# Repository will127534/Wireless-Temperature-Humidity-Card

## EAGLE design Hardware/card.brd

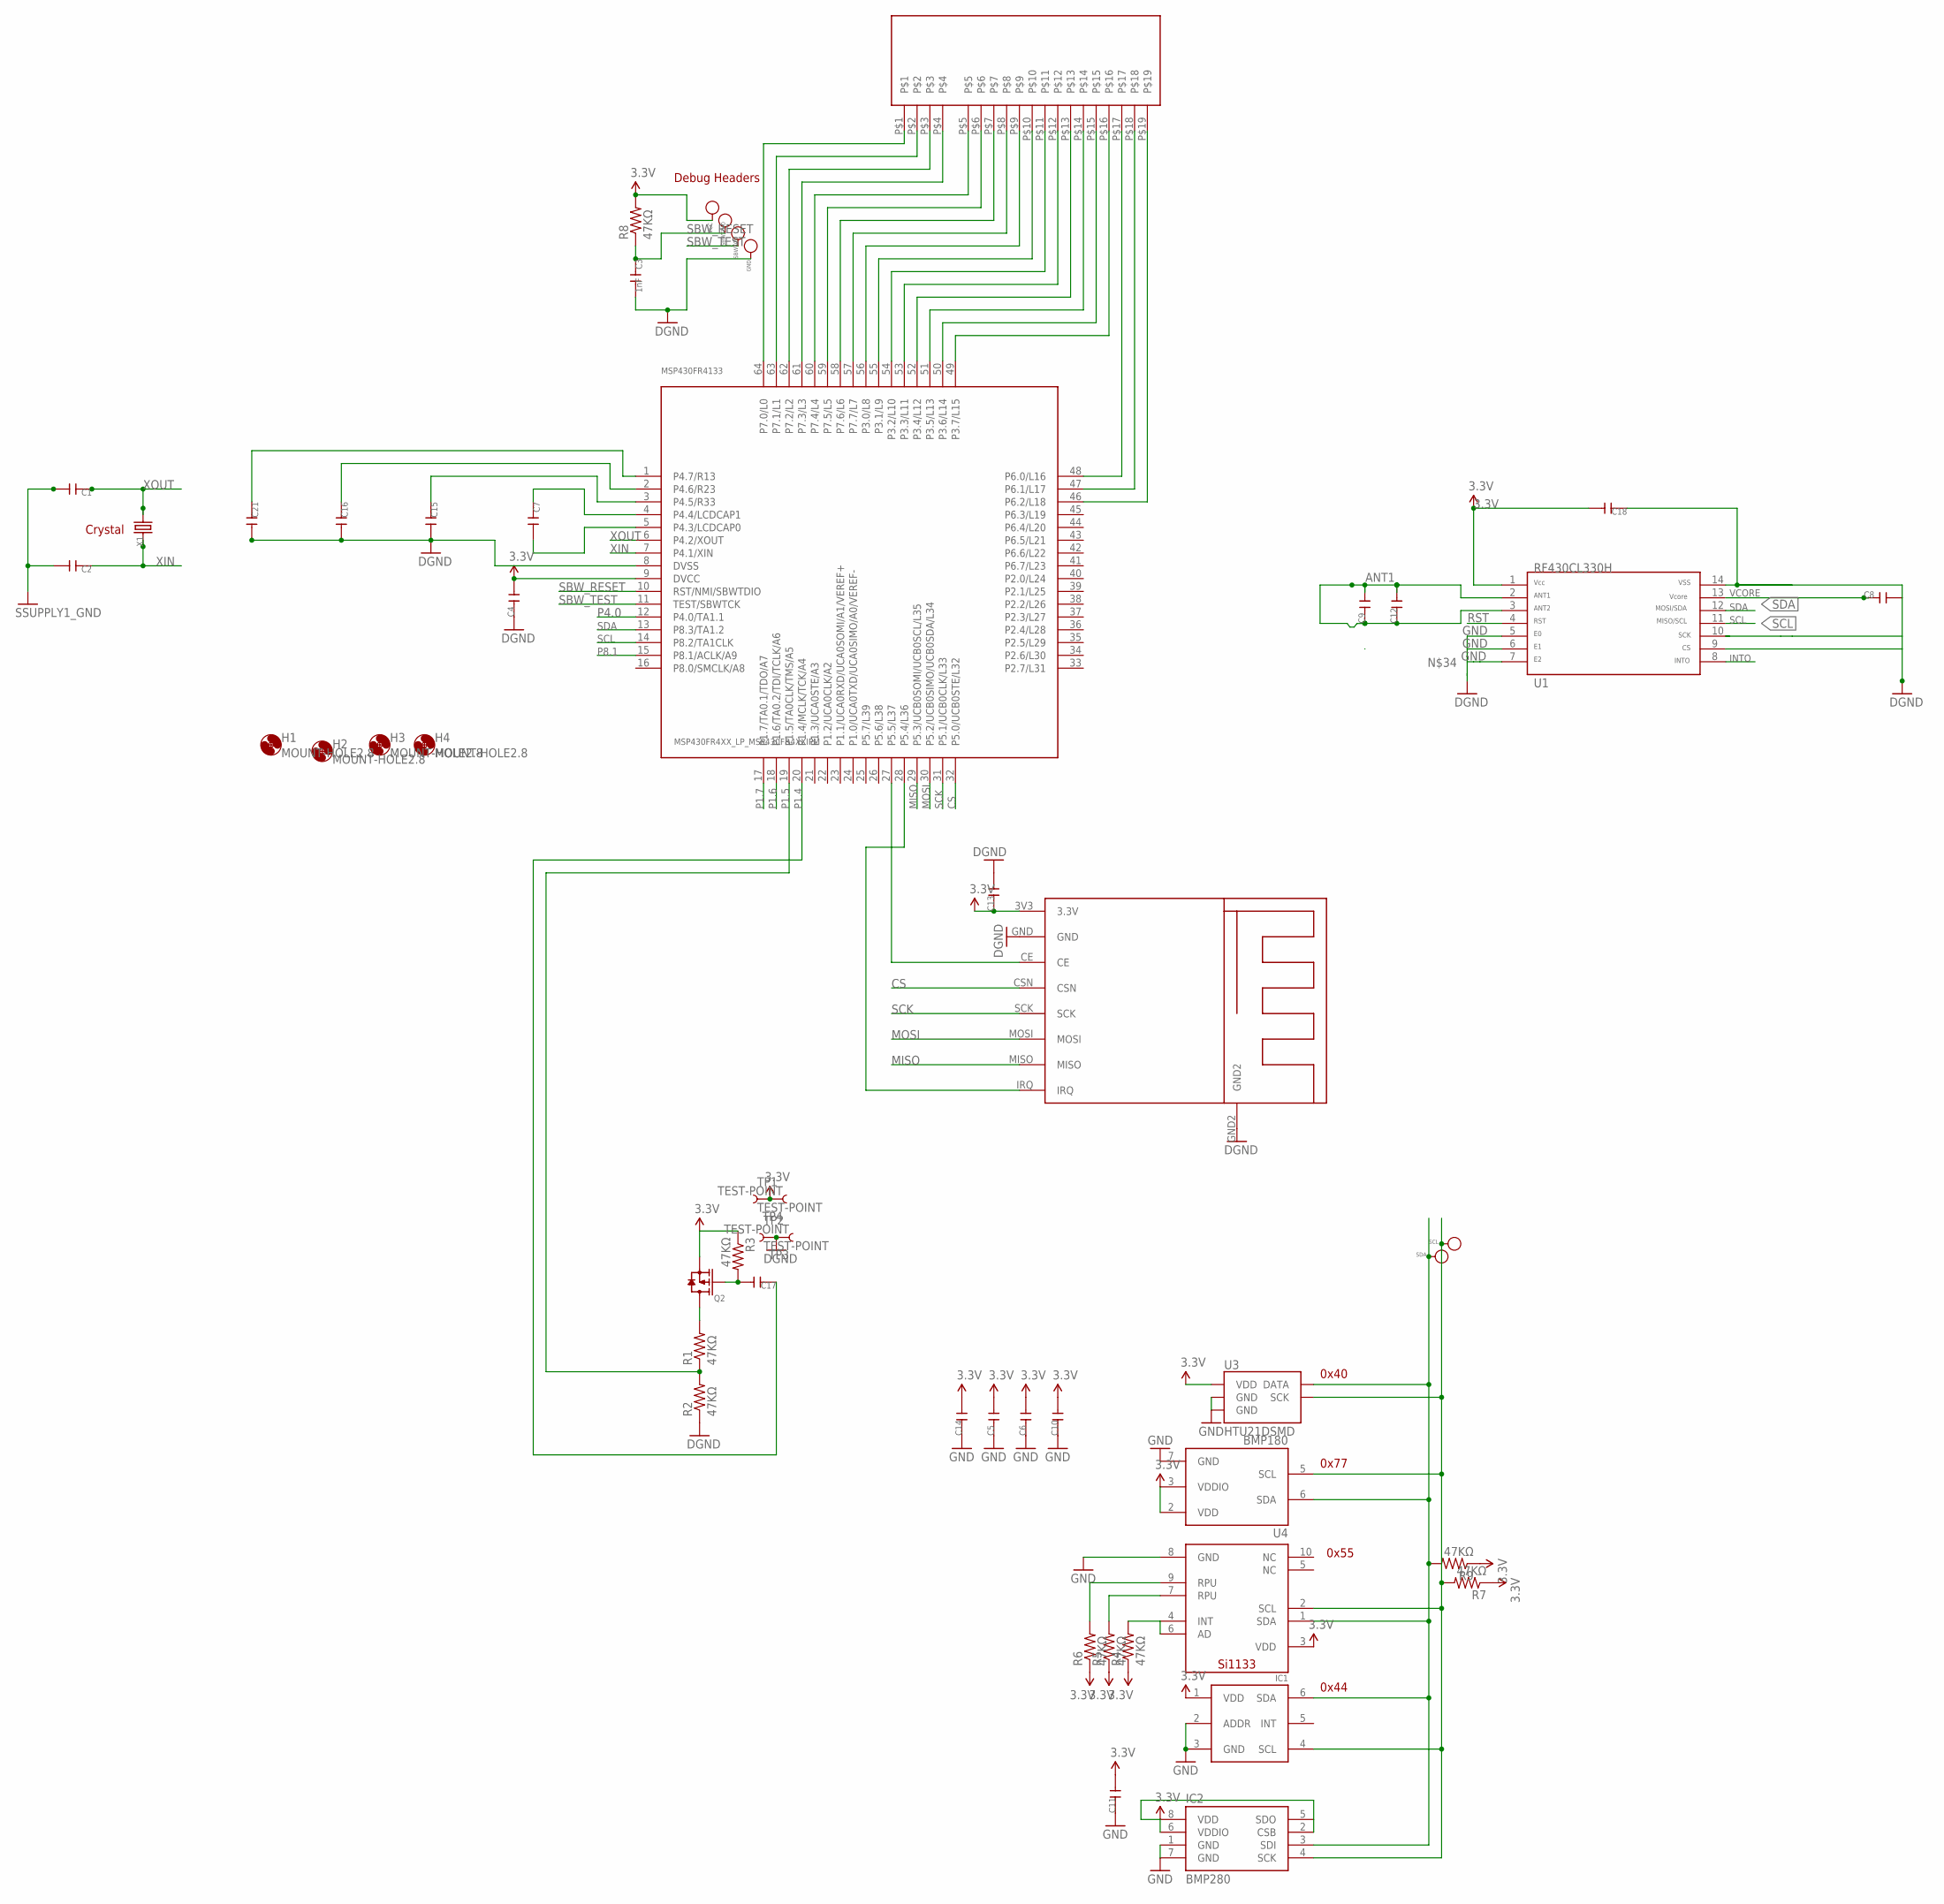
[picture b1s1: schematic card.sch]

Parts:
C1, C2, C4, C5, C6, C7, C8, C9, C10, C11, C12, C14, C15, C16, C17, C18, C21: C-0402; C0402
C3: 1nF; C0402
C13: C-0603; C0603
GND: PAD-TEST-POINT'4545'; TP_4545
H1, H2, H3, H4: MOUNT-HOLE2.8; 2,8
IC1: SILICONLABS-SI1133
IC2: BMP280; LGA
MSP430FR4133: MSP430FR4XX_LP_MSP430FR4XXIPM; MSP430G6_LP_LQFP64
Q2: MOSFET-P'SI2323CDS/SI2305DS<BR>'; SOT23
R1, R2, R3, R4, R5, R6, R7, R8, R9: 47KΩ; RCL_R1005
SBWTCK: PAD-TEST-POINT'4545'; TP_4545
SBWTDIO: PAD-TEST-POINT'4545'; TP_4545
SCL: PAD-TEST-POINT'4545'; TP_4545
SDA: PAD-TEST-POINT'4545'; TP_4545
TP1, TP2, TP3, TP4: TEST-POINT; BATTERY
U1: RF430CL330H; PW14
U3: HTU21DSMD; HTU21D
U4: BMP180
U$1: HUMIDITYTEMP_DISPLAY
U$2: NRF24MINI
U$5: TI-OPT3001
VCC: PAD-TEST-POINT'4545'; TP_4545
X1: CRYSTAL-3215; 2P-SMD-3.2X1.5

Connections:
3.3V: C4.2, C5.2, C6.2, C10.2, C11.2, C13.1, C14.2, C18.2, IC1.3 (VDD), IC2.2 (CSB), IC2.5 (SDO), IC2.6 (VDDIO), IC2.8 (VDD), MSP430FR4133.9 (DVCC), Q2.2 (S), R3.1, R4.1, R5.1, R6.1, R7.1, R8.2, R9.1, TP1.P$1, TP4.P$1, U1.1, U3.VDD, U4.2 (VDD), U4.3 (VDDIO), U$2.3V3 (3.3V), U$5.1 (VDD), VCC.T
ANT1: C9.1, C9.2, C12.1, C12.2, U1.2, U1.3
CS: MSP430FR4133.32 (P5.0/UCB0STE/L32), U$2.CSN
GND: C1.2, C2.2, C3.2, C4.1, C5.1, C6.1, C8.2, C10.1, C11.1, C13.2, C14.1, C15.2, C16.2, C18.1, C21.2, GND.T, IC1.8 (GND), IC2.1 (GND), IC2.7 (GND), MSP430FR4133.8 (DVSS), R2.1, TP2.P$1, TP3.P$1, U1.5, U1.6, U1.7, U1.9, U1.10, U1.14, U3.7 (GND), U3.GND, U4.7 (GND), U$2.GND, U$2.GND2, U$5.2 (ADDR), U$5.3 (GND)
INTO: U1.8
MISO: MSP430FR4133.29 (P5.3/UCB0SOMI/UCB0SCL/L35), U$2.MISO
MOSI: MSP430FR4133.30 (P5.2/UCB0SIMO/UCB0SDA/L34), U$2.MOSI
unnamed: MSP430FR4133.27 (P5.5/L37), U$2.CE
unnamed: MSP430FR4133.28 (P5.4/L36), U$2.IRQ
unnamed: MSP430FR4133.64 (P7.0/L0), U$1.P$1
unnamed: MSP430FR4133.63 (P7.1/L1), U$1.P$2
unnamed: MSP430FR4133.62 (P7.2/L2), U$1.P$3
unnamed: MSP430FR4133.61 (P7.3/L3), U$1.P$4
unnamed: Q2.3 (D), R1.2
unnamed: MSP430FR4133.60 (P7.4/L4), U$1.P$5
unnamed: MSP430FR4133.59 (P7.5/L5), U$1.P$6
unnamed: MSP430FR4133.58 (P7.6/L6), U$1.P$7
unnamed: MSP430FR4133.57 (P7.7/L7), U$1.P$8
unnamed: MSP430FR4133.56 (P3.0/L8), U$1.P$9
unnamed: MSP430FR4133.55 (P3.1/L9), U$1.P$10
unnamed: MSP430FR4133.54 (P3.2/L10), U$1.P$11
unnamed: MSP430FR4133.53 (P3.3/L11), U$1.P$12
unnamed: MSP430FR4133.52 (P3.4/L12), U$1.P$13
unnamed: MSP430FR4133.51 (P3.5/L13), U$1.P$14
unnamed: MSP430FR4133.50 (P3.6/L14), U$1.P$15
unnamed: MSP430FR4133.49 (P3.7/L15), U$1.P$16
unnamed: MSP430FR4133.48 (P6.0/L16), U$1.P$17
unnamed: MSP430FR4133.47 (P6.1/L17), U$1.P$18
unnamed: IC1.4 (INT), IC1.6 (AD), R4.2
unnamed: MSP430FR4133.46 (P6.2/L18), U$1.P$19
unnamed: C21.1, MSP430FR4133.1 (P4.7/R13)
unnamed: C16.1, MSP430FR4133.2 (P4.6/R23)
unnamed: C15.1, MSP430FR4133.3 (P4.5/R33)
unnamed: C7.1, MSP430FR4133.4 (P4.4/LCDCAP1)
unnamed: C7.2, MSP430FR4133.5 (P4.3/LCDCAP0)
unnamed: IC1.9 (RPU), R6.2
unnamed: IC1.7 (RPU), R5.2
unnamed: C17.2, Q2.1 (G), R3.2
P1.4: MSP430FR4133.19 (P1.5/TA0CLK/TMS/A5), R1.1, R2.2
P1.5: C17.1, MSP430FR4133.20 (P1.4/MCLK/TCK/A4)
P1.6: MSP430FR4133.18 (P1.6/TA0.2/TDI/TCLK/A6)
P1.7: MSP430FR4133.17 (P1.7/TA0.1/TDO/A7)
P4.0: MSP430FR4133.12 (P4.0/TA1.1)
P8.1: MSP430FR4133.15 (P8.1/ACLK/A9)
RST: U1.4
SBW_RESET: C3.1, MSP430FR4133.10 (RST/NMI/SBWTDIO), R8.1, SBWTDIO.T
SBW_TEST: MSP430FR4133.11 (TEST/SBWTCK), SBWTCK.T
SCK: MSP430FR4133.31 (P5.1/UCB0CLK/L33), U$2.SCK
SCL: IC1.2 (SCL), IC2.4 (SCK), MSP430FR4133.14 (P8.2/TA1CLK), R7.2, SCL.T, U1.11, U3.SCK, U4.5 (SCL), U$5.4 (SCL)
SDA: IC1.1 (SDA), IC2.3 (SDI), MSP430FR4133.13 (P8.3/TA1.2), R9.2, SDA.T, U1.12, U3.DATA, U4.6 (SDA), U$5.6 (SDA)
VCORE: C8.1, U1.13
XIN: C2.1, MSP430FR4133.7 (P4.1/XIN), X1.1
XOUT: C1.1, MSP430FR4133.6 (P4.2/XOUT), X1.2

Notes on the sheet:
Debug Headers
Crystal
0x40
0x77
0x44
0x55

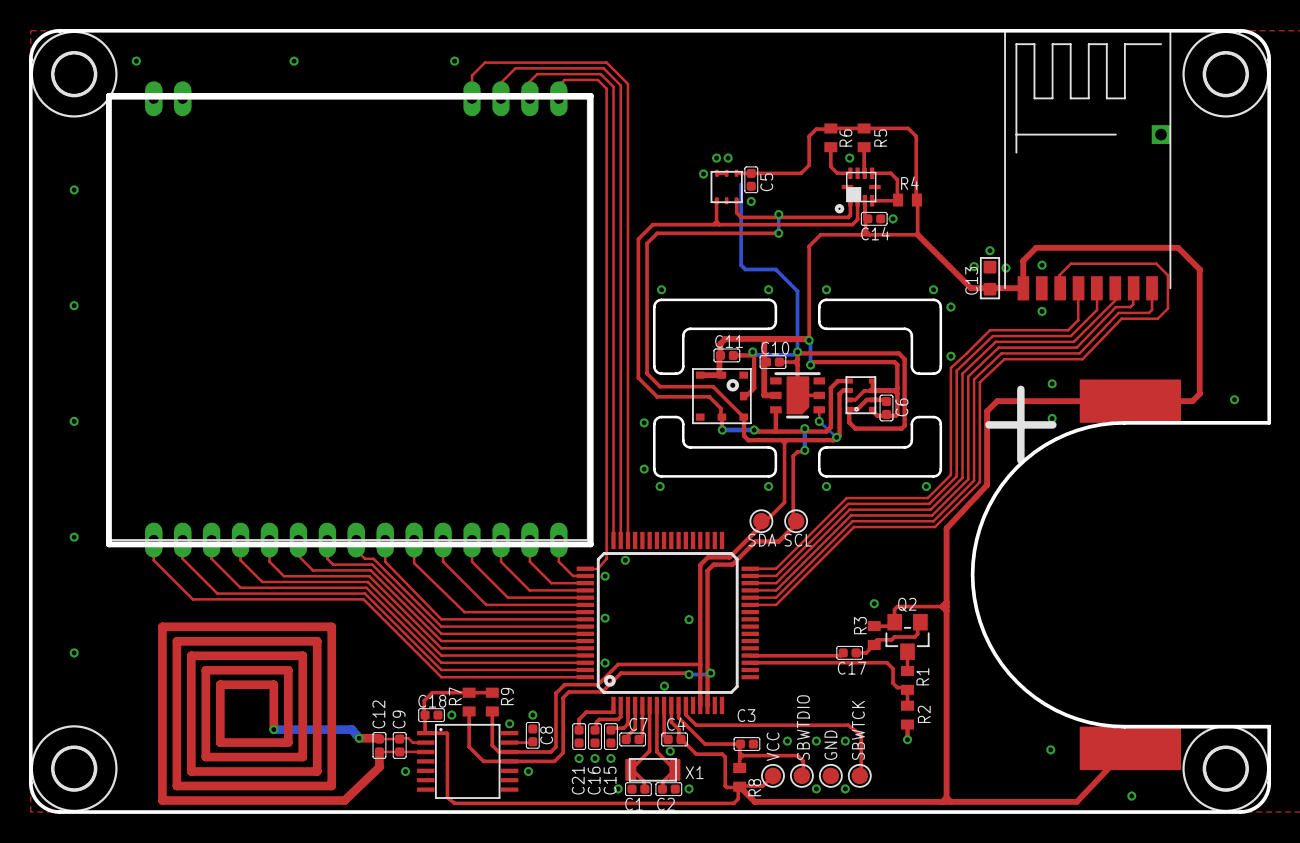
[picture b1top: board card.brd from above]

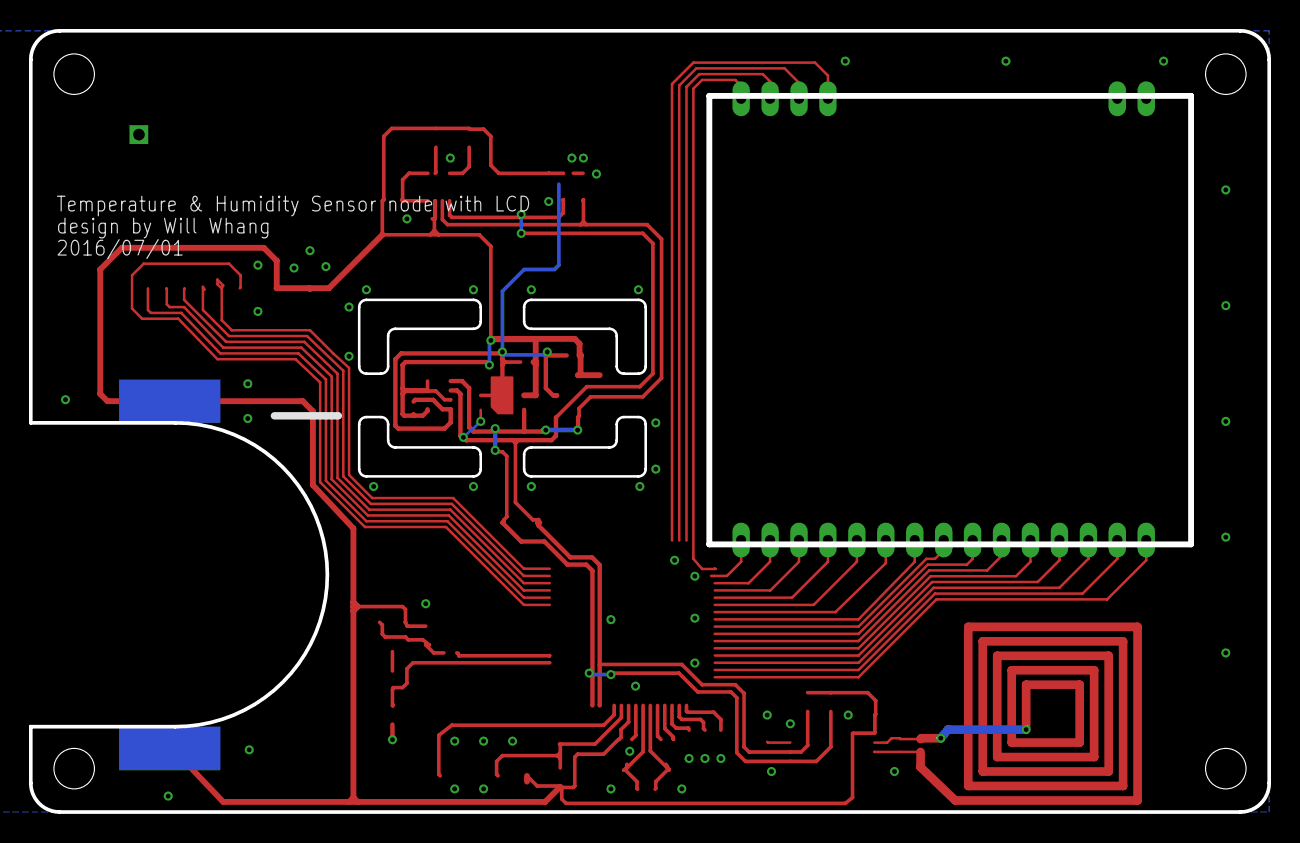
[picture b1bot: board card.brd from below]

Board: 2 copper layers, 85.4 x 53.8 mm, 53 parts (2 on the bottom side), 47 nets.

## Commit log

2017-12-05 init ver1

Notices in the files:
parts and their libraries:
SparkFun-Sensors: Licensing: CC v3.0 Share-Alike You are welcome to use this library for commercial purposes.
SparkFun-Displays: Licensing: Creative Commons ShareAlike 4.0 International - https://creativecommons.org/licenses/by-sa/4.0
